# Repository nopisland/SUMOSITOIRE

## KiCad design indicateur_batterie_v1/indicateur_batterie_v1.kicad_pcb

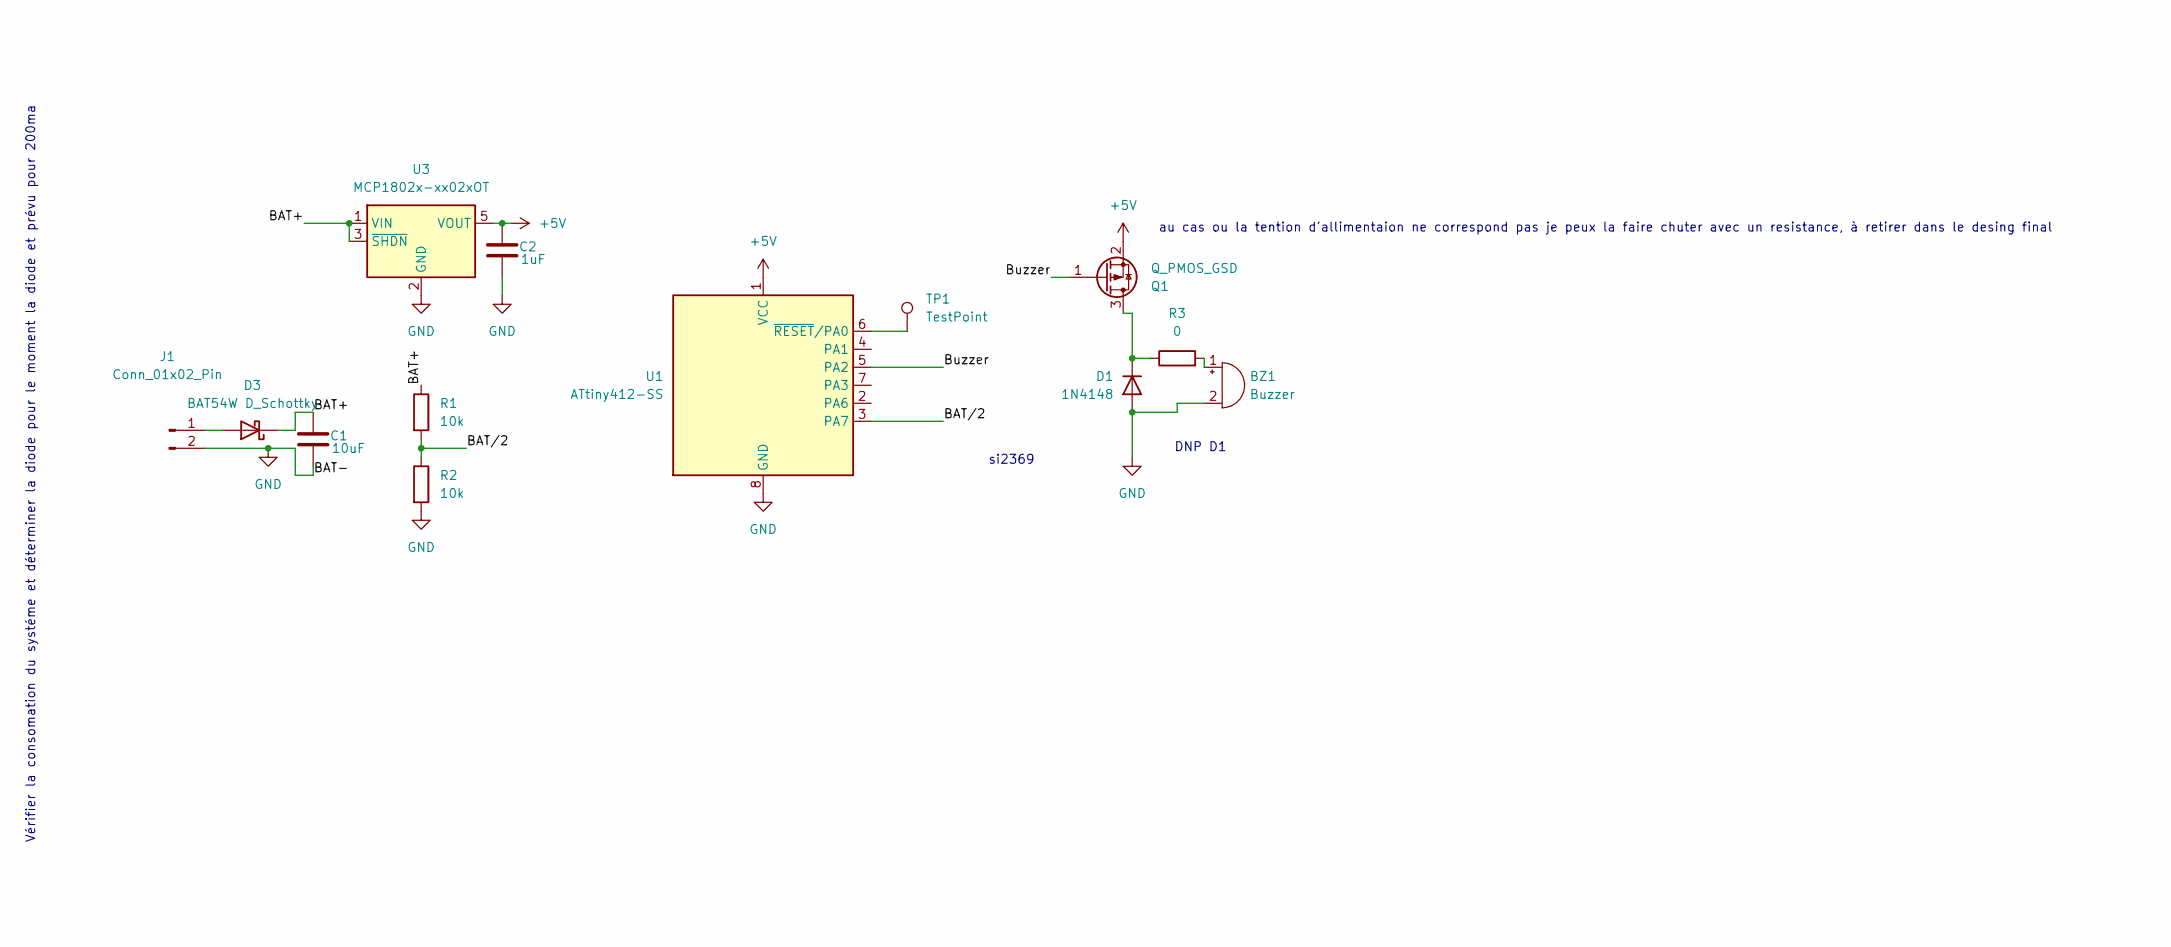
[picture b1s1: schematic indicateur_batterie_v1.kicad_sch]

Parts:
BZ1: Buzzer; Buzzer_TDK_PS1240P02BT_D12.2mm_H6.5mm
C1: 10uF; C_1206_3216Metric
C2: 1uF; C_0603_1608Metric
D1: 1N4148; D_DO-35_SOD27_P7.62mm_Horizontal
D3: BAT54W D_Schottky; D_SOD-123
J1: Conn_01x02_Pin; PinSocket_1x02_P2.54mm_Vertical
Q1: Q_PMOS_GSD; TSOT-23
R1, R2: 10k; R_0603_1608Metric
R3: 0; R_0603_1608Metric
TP1: TestPoint; TestPoint_Pad_2.0x2.0mm
U1: ATtiny412-SS; SOIC-8_3.9x4.9mm_P1.27mm
U3: MCP1802x-xx02xOT; SOT-23-5

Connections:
+5V: C2.1, Q1.2 (S), U1.1 (VCC), U3.5 (VOUT)
/BAT+: C1.1, D3.1 (K), R1.1, U3.1 (VIN), U3.3 (~SHDN)
/BAT/2: R1.2, R2.1, U1.3 (PA7)
/Buzzer: Q1.1 (G), U1.5 (PA2)
GND: BZ1.2 (-), C1.2, C2.2, D1.2 (A), J1.2, R2.2, U1.8 (GND), U3.2 (GND)
unnamed: BZ1.1 (+), R3.2
unnamed: D1.1 (K), Q1.3 (D), R3.1
unnamed: D3.2 (A), J1.1
unnamed: TP1.1, U1.6 (~RESET/PA0)

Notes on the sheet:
au cas ou la tention d'allimentaion ne correspond pas je peux la faire chuter avec un resistance, à retirer dans le desing final
si2369
Vérifier la consomation du systéme et déterminer la diode pour le moment la diode et prévu pour 200ma
DNP D1

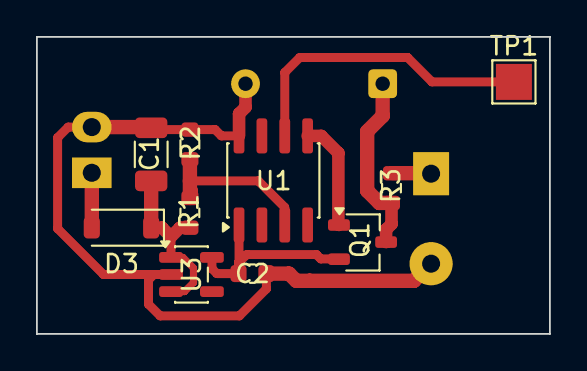
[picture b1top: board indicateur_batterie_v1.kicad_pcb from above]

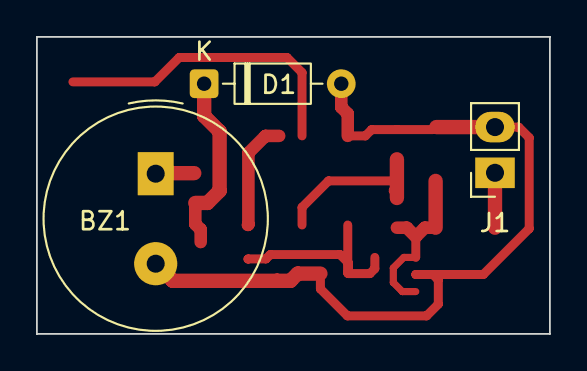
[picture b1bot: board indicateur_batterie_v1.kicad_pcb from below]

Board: 2 copper layers, 28.5 x 16.5 mm, 13 parts (3 on the bottom side), 9 nets.

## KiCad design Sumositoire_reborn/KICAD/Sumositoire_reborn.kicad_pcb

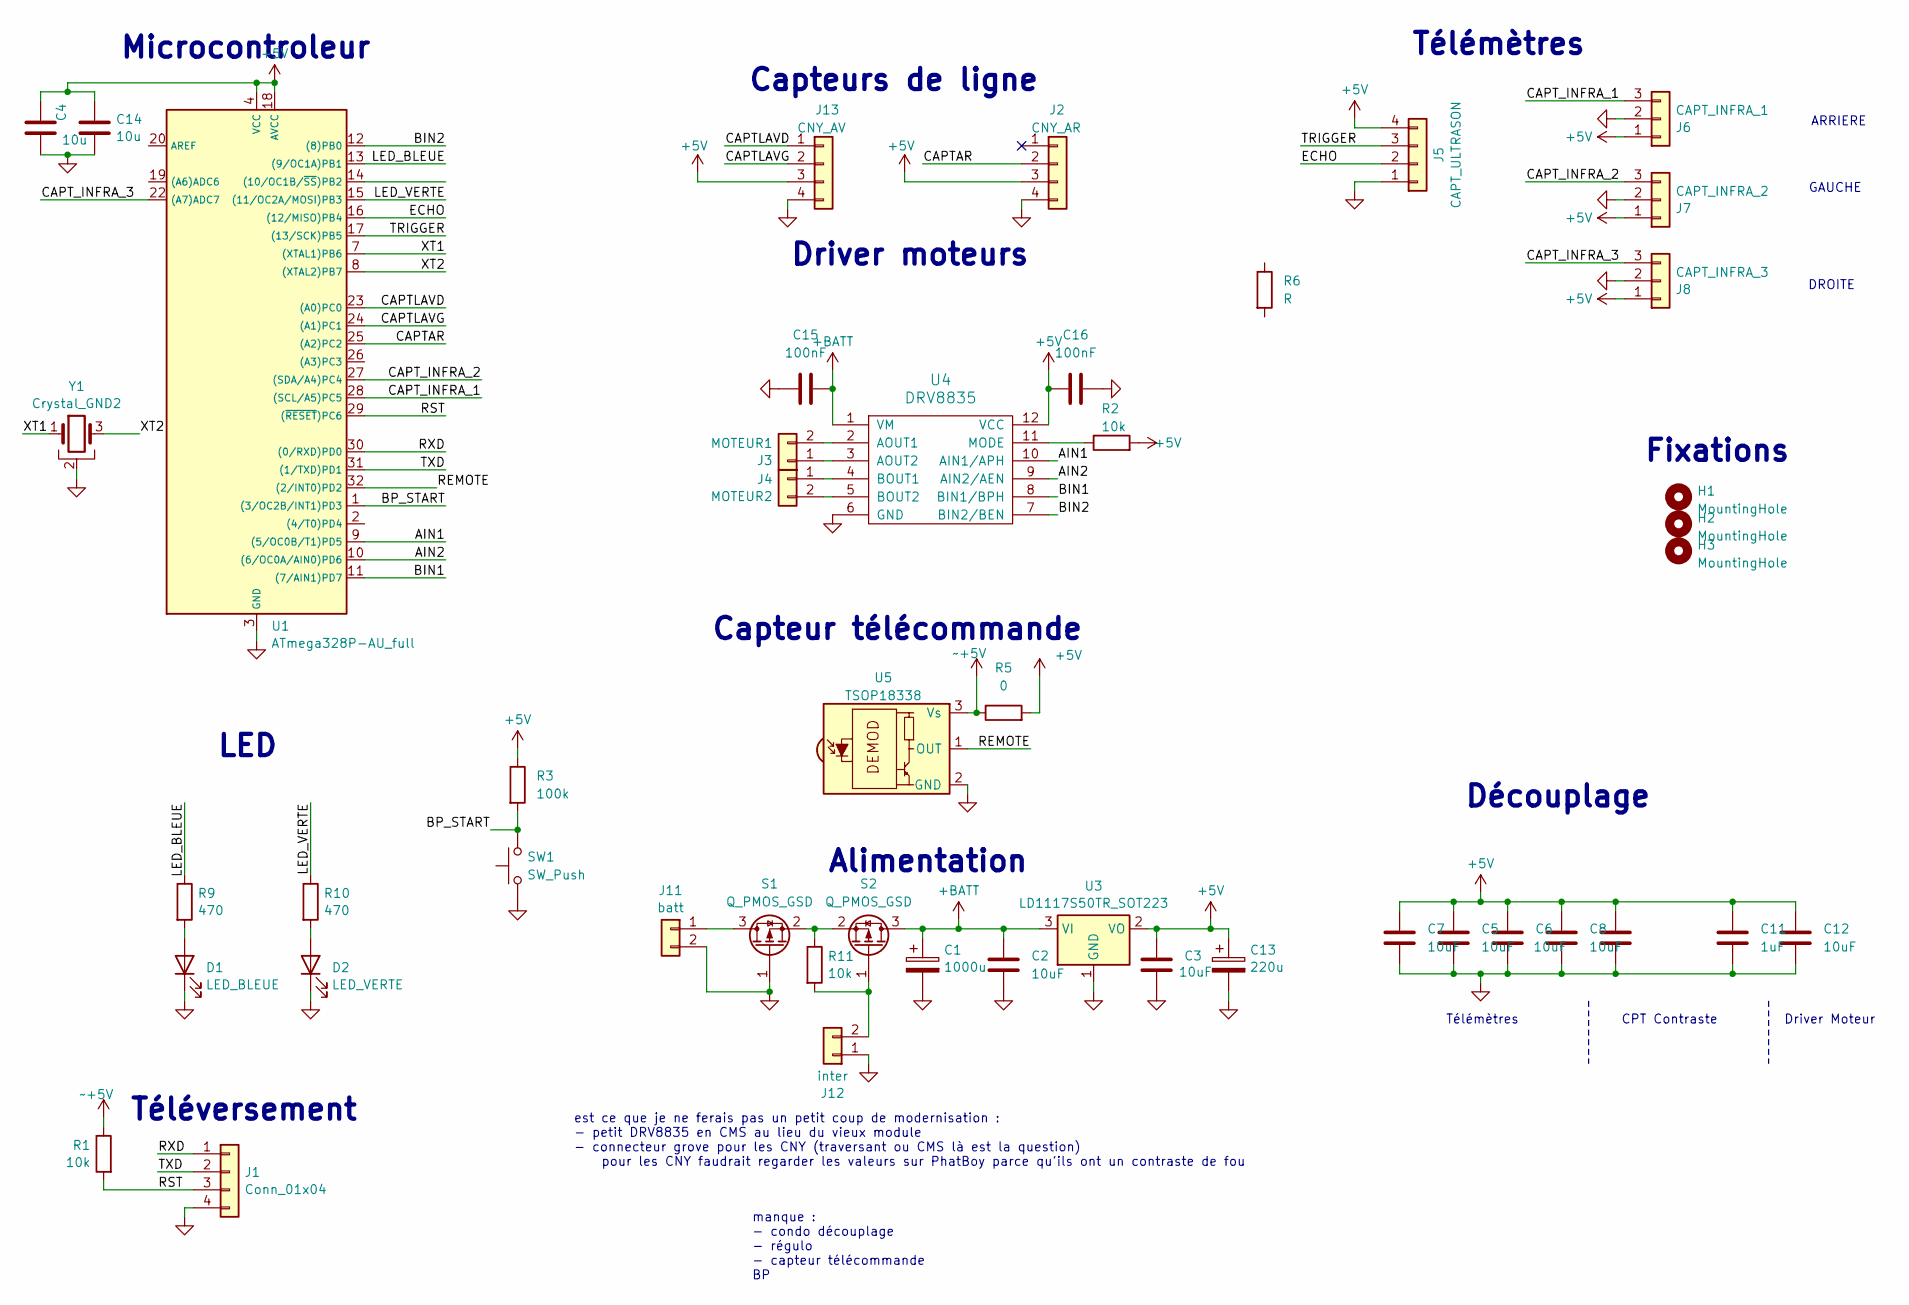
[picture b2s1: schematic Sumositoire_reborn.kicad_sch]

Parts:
C1: 1000u; CP_Elec_10x10
C2: 10uF; C_0603_1608Metric
C3, C5, C6, C7, C8, C12: 10uF; C_1206_3216Metric
C4, C14: 10u; C_1206_3216Metric
C9, C11: 1uF; C_1206_3216Metric
C13: 220u; C_1206_3216Metric
C15, C16: 100nF; C_0603_1608Metric
D1: LED_BLEUE; LED_1206_3216Metric
D2: LED_VERTE; LED_1206_3216Metric
H1, H2, H3: MountingHole; MountingHole_3.2mm_M3_DIN965_Pad
J1: Conn_01x04; PinSocket_1x04_P2.54mm_Vertical
J2: CNY_AR; GROVE_HY2.0_VERTICAL_SMD
J3: MOTEUR1; PinHeader_1x02_P2.54mm_Horizontal
J4: MOTEUR2; PinHeader_1x02_P2.54mm_Horizontal
J5: CAPT_ULTRASON; PinHeader_1x04_P2.54mm_Horizontal
J6: CAPT_INFRA_1; PinHeader_1x03_P2.54mm_Horizontal
J7: CAPT_INFRA_2; PinHeader_1x03_P2.54mm_Horizontal
J8: CAPT_INFRA_3; PinHeader_1x03_P2.54mm_Horizontal
J11: batt; PinHeader_1x02_P2.54mm_Horizontal
J12: inter; PinHeader_1x02_P2.54mm_Horizontal
J13: CNY_AV; GROVE_HY2.0_VERTICAL_SMD
R1, R2, R11: 10k; R_0603_1608Metric
R3: 100k; R_0603_1608Metric
R5: 0; R_0603_1608Metric
R6: R; D_1206_3216Metric
R9, R10: 470; R_0603_1608Metric
S1, S2: Q_PMOS_GSD; TSOT-23
SW1: SW_Push; BP_Schruter_LSH
U1: ATmega328P-AU_full; TQFP32m
U3: LD1117S50TR_SOT223; SOT-223-3_TabPin2
U4: DRV8835; WSON-12
U5: TSOP18338; Vishay_MOLD-3Pin
Y1: Crystal_GND2; osc_CSTNE

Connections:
+5V: C3.1, C4.1, C5.1, C6.1, C7.1, C8.1, C9.1, C11.1, C12.1, C13.1, C14.1, C16.1, J2.3, J5.4, J6.1, J7.1, J8.1, J13.3, R2.2, R3.1, R5.2, U1.4 (VCC), U1.6 (VCC), U1.18 (AVCC), U3.2 (VO), U4.12 (VCC)
+BATT: C1.1, C2.1, C15.2, S2.3 (D), U3.3 (VI), U4.1 (VM)
/AIN1: U1.9 ((5/OC0B/T1)PD5), U4.10 (AIN1/APH)
/AIN2: U1.10 ((6/OC0A/AIN0)PD6), U4.9 (AIN2/AEN)
/BIN1: U1.11 ((7/AIN1)PD7), U4.8 (BIN1/BPH)
/BIN2: U1.12 ((8)PB0), U4.7 (BIN2/BEN)
/BP_START: R3.2, SW1.2, U1.1 ((3/OC2B/INT1)PD3)
/CAPTAR: J2.2, U1.25 ((A2)PC2)
/CAPTLAVD: J13.1, U1.23 ((A0)PC0)
/CAPTLAVG: J13.2, U1.24 ((A1)PC1)
/CAPT_INFRA_1: J6.3, U1.28 ((SCL/A5)PC5)
/CAPT_INFRA_2: J7.3, U1.27 ((SDA/A4)PC4)
/CAPT_INFRA_3: J8.3, U1.22 ((A7)ADC7)
/ECHO: J5.2, U1.16 ((12/MISO)PB4)
/LED_BLEUE: R9.1, U1.13 ((9/OC1A)PB1)
/LED_VERTE: R10.1, U1.15 ((11/OC2A/MOSI)PB3)
/REMOTE: U1.32 ((2/INT0)PD2), U5.1 (OUT)
/RST: J1.3, R1.2, U1.29 ((~RESET)PC6)
/RXD: J1.1, U1.30 ((0/RXD)PD0)
/TRIGGER: J5.3, U1.17 ((13/SCK)PB5)
/TXD: J1.2, U1.31 ((1/TXD)PD1)
/XT1: U1.7 ((XTAL1)PB6), Y1.1
/XT2: U1.8 ((XTAL2)PB7), Y1.3
GND: C1.2, C2.2, C3.2, C4.2, C5.2, C6.2, C7.2, C8.2, C9.2, C11.2, C12.2, C13.2, C14.2, C15.1, C16.2, D1.1 (K), D2.1 (K), J1.4, J2.4, J5.1, J6.2, J7.2, J8.2, J11.2, J12.1, J13.4, S1.1 (G), SW1.1, U1.3 (GND), U1.5 (GND), U1.21 (GND), U3.1 (GND), U4.6 (GND), U5.2 (GND), Y1.2
unnamed: D1.2 (A), R9.2
unnamed: D2.2 (A), R10.2
unnamed: J3.1, U4.3 (AOUT2)
unnamed: J3.2, U4.2 (AOUT1)
unnamed: J4.1, U4.4 (BOUT1)
unnamed: J4.2, U4.5 (BOUT2)
unnamed: J11.1, S1.3 (D)
unnamed: J12.2, R11.2, S2.1 (G)
unnamed: R11.1, S1.2 (S), S2.2 (S)
unnamed: R2.1, U4.11 (MODE)
~+5V: R1.1, R5.1, U5.3 (Vs)

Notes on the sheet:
Microcontroleur
Driver Moteur
Télémètres
CPT Contraste
GAUCHE
est ce que je ne ferais pas un petit coup de modernisation : - petit DRV8835 en CMS au lieu du vieux module - connecteur grove pour les CNY (traversant ou CMS là est la question) pour les CNY faudrait regarder les valeurs sur PhatBoy parce qu'ils ont un contraste de fou
LED
manque : - condo découplage - régulo - capteur télécommande BP
Téléversement
Fixations
Alimentation
ARRIERE
Capteur télécommande
DROITE
Découplage
Capteurs de ligne
Driver moteurs

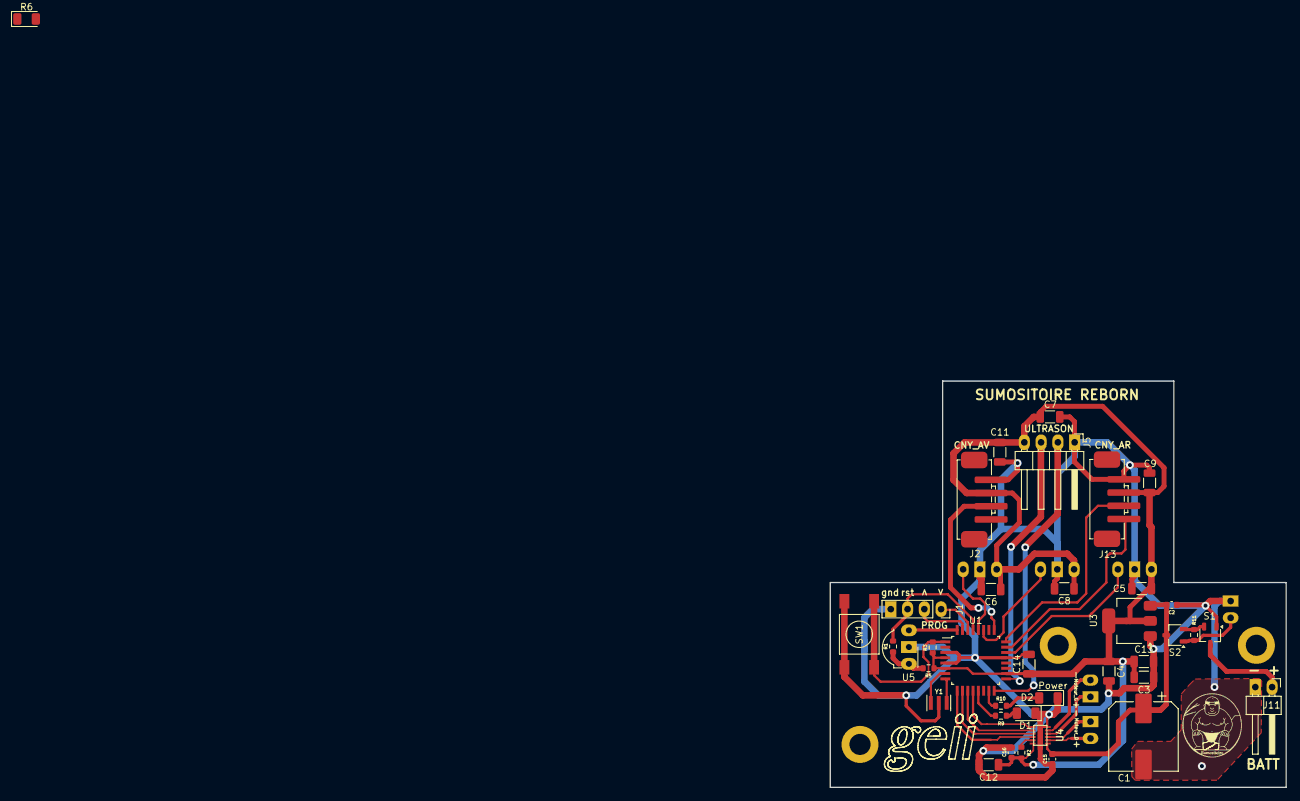
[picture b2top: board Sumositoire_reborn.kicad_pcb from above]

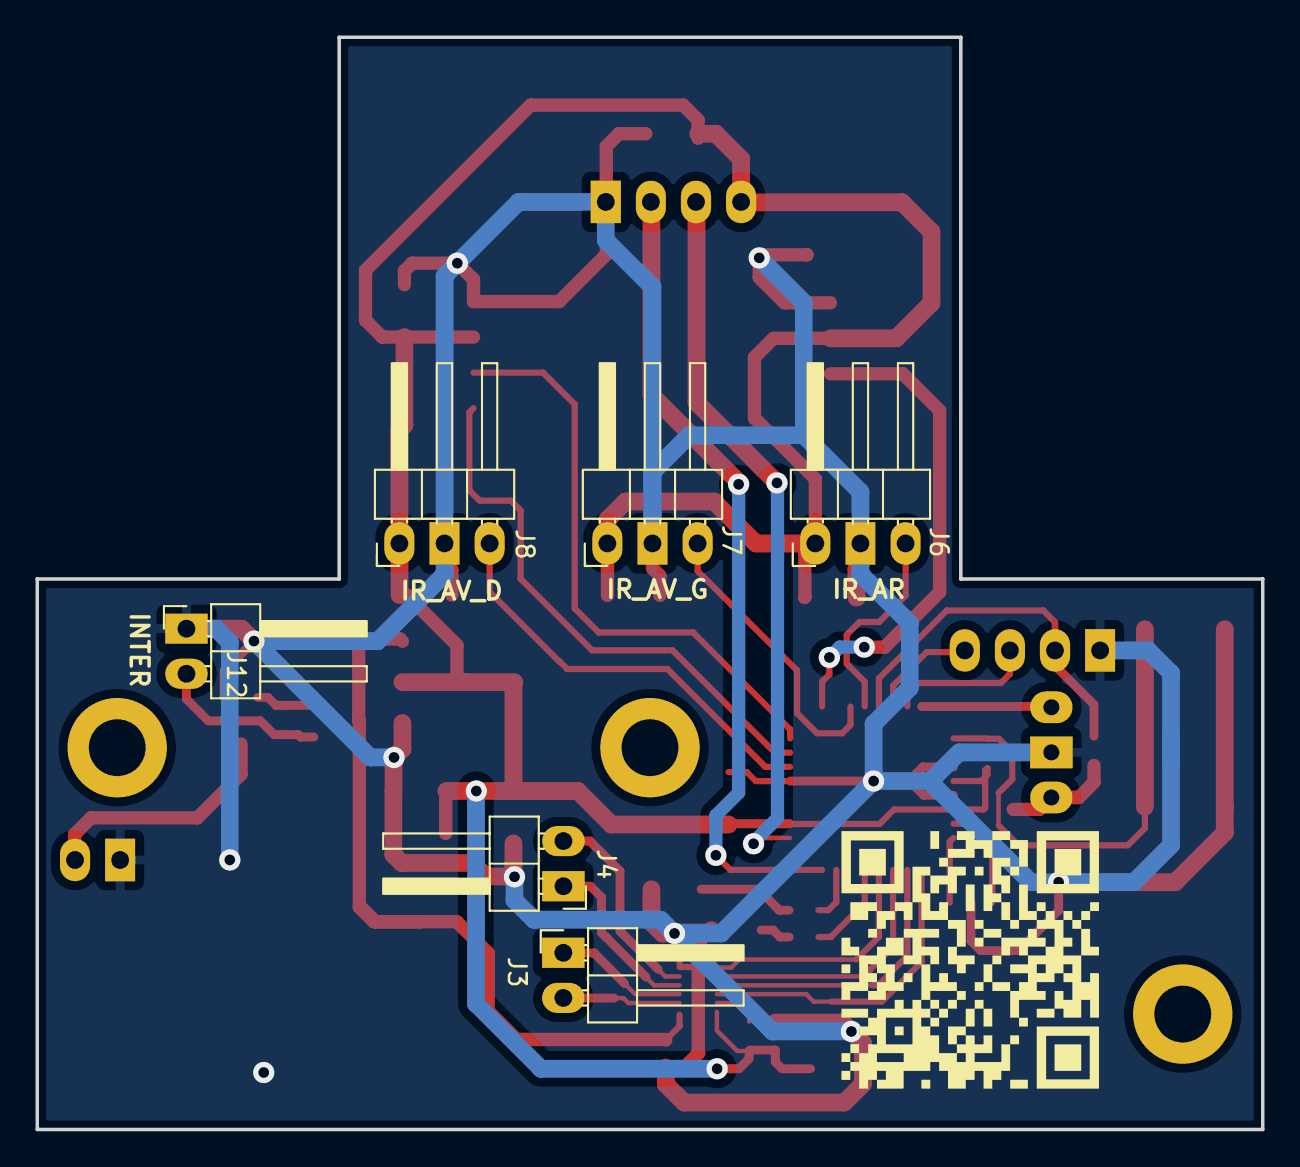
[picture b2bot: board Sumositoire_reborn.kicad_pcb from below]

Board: 2 copper layers, 69.0 x 61.5 mm, 48 parts (6 on the bottom side), 35 nets.

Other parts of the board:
Ref**: Val**; logo_geii_fsilk

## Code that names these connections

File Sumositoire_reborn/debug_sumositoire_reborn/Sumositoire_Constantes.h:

#define remote 2

/*#define TOUT_DROIT 1
#define MARCHE_ARRIERE 2
#define DROITE 3
#define GAUCHE 4
#define STOP 5
*/

//sharp
#define pin1 A5  //sharp arrier
#define pin2 A4 //sharp gauche
#define pin3 A7 //sharp droite
int sueil_infra_arierre = 5;
int sueil_infra_droite = 30;
int sueil_infra_gauche = 30;
#define SHAR 16
#define SHG 32
#define SHD 64

//Ligne var
int input_ligne_ar = A2;
#define AR 1

int input_ligne_av_G = A1;
#define AVG 2

int input_ligne_av_D = A0;
#define AVD 4

double value1, distance1, value2, distance2, value3, distance3;
int valeur_arl, valeur_avg, valeur_avd;

//US var
int trig = 13;
int echo = 12;
long lecture_echo;
long cm;
int sueil_ultrason = 50; // meusure en cm
#define US 8


// Motors
const byte moteur_gauche[] = {8, 7}; //Bin2_-_Bin1
const byte moteur_droite[] = {6, 5}; //Ain2_-_Ain1
enum { TOUT_DROIT = 1, MARCHE_ARRIERE, GAUCHE, DROITE, STOP};

//led
const byte led_g = 11, led_b = 9;
//button
const byte button = 3;

byte arret = 0;

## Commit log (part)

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2026-01-16 ajout du QR_code
2026-01-22 création de fichier gerber
2026-02-10 indicateur batterie
2026-03-27 changement déclanchement télécomande
2026-04-01 suppression du démarrage avec le pb poussoir
2026-04-10 psuh
